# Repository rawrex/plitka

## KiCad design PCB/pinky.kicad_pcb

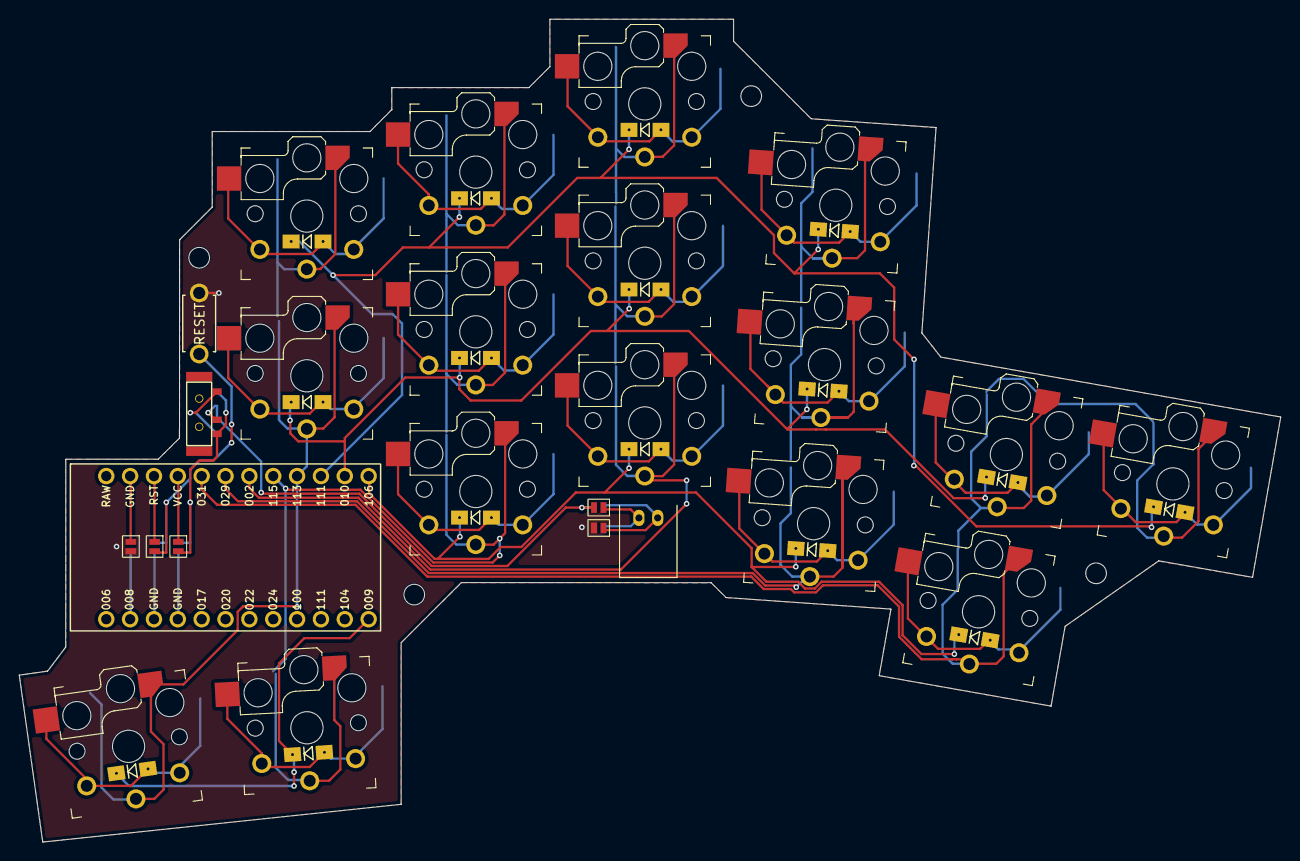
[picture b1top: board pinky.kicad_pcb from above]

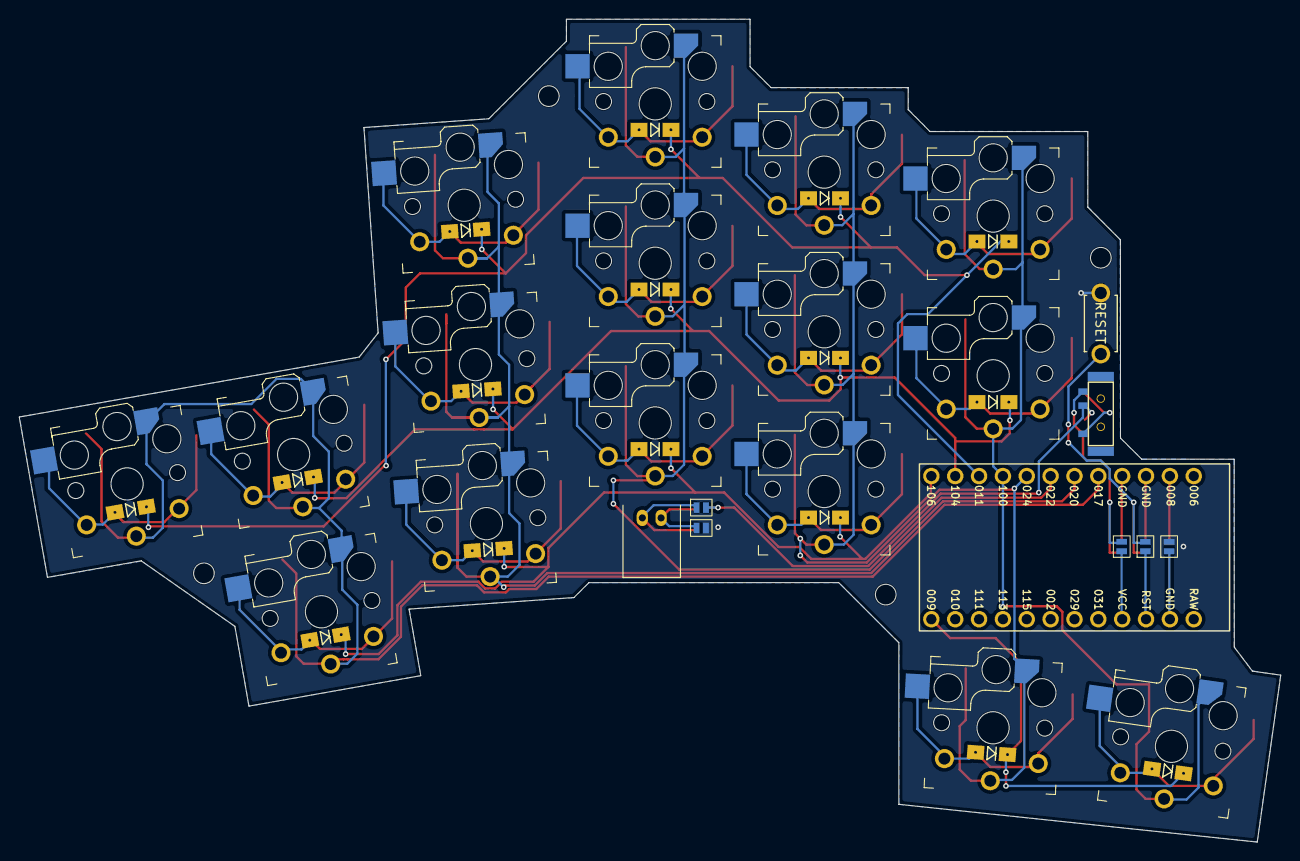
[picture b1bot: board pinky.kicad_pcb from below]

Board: 2 copper layers, 134.3 x 87.6 mm, 50 parts (6 on the bottom side), 34 nets.

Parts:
BT1: JST_PH
D1, D2, D4, D5, D6, D7, D8, D9, D10, D11, D12, D13, D14, D15, D16, D17: D; D_SOD123
H1, H2, H3, H4: MountingHole_2.2mm_M2; MountingHole
JP1, JP2, JP3, JP4, JP5, JP6, JP7, JP8, JP9, JP10: SDA; Jumper
RESET19: Val**; ResetSW
SW2, SW3, SW5, SW6, SW7, SW8, SW9, SW10, SW11, SW12, SW13, SW14, SW15, SW16, SW17, SW18: SW_Kailh_Choc_PG1350; Switch
SW_PWR1: MSK12C02
U1: nice!nano; nice_nano

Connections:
+BATT: JP9.2, JP10.2, SW_PWR1.3 (A)
+BATT_indirect: JP9.1, JP10.1, U1.4 (GND), U1.16 (EXT_VCC)
/PAD1: BT1.1 (+), JP1.1, JP2.1
/PAD2: BT1.2 (-), JP3.1, JP4.1
GND: JP1.2, JP4.2, JP5.2, JP6.2, RESET19.1
GND_indirect: JP5.1, JP6.1, U1.2 (D0/P0.08), U1.14 (GND)
unnamed: D1.2 (A), SW2.2
unnamed: D2.2 (A), SW3.2
unnamed: D4.2 (A), SW5.2
unnamed: D5.2 (A), SW6.2
unnamed: D6.2 (A), SW7.2
unnamed: D7.2 (A), SW8.2
unnamed: D8.2 (A), SW9.2
unnamed: D9.2 (A), SW10.2
unnamed: D10.2 (A), SW11.2
unnamed: D11.2 (A), SW12.2
unnamed: D12.2 (A), SW13.2
unnamed: D13.2 (A), SW14.2
unnamed: D14.2 (A), SW15.2
unnamed: D15.2 (A), SW16.2
unnamed: D16.2 (A), SW17.2
unnamed: D17.2 (A), SW18.2
unnamed: JP2.2, JP3.2, SW_PWR1.2 (B)
RESET: JP7.2, JP8.2, RESET19.2
RESET_indirect: JP7.1, JP8.1, U1.3 (GND), U1.15 (RESET)
col_A: SW2.1, SW3.1, SW5.1, U1.9 (D6/P1.00)
col_B: SW6.1, SW7.1, SW8.1, SW9.1, U1.8 (D5/P0.24)
col_C: SW10.1, SW11.1, SW12.1, U1.7 (D4/P0.22)
col_D: SW13.1, SW14.1, SW15.1, U1.6 (D3/P0.20)
col_E: SW16.1, SW17.1, SW18.1, U1.5 (D2/P0.17)
row_A: D1.1 (K), D5.1 (K), D9.1 (K), D12.1 (K), D15.1 (K), U1.10 (D7/P0.11)
row_B: D2.1 (K), D6.1 (K), D10.1 (K), D13.1 (K), D16.1 (K), U1.11 (D8/P1.04)
row_C: D7.1 (K), D11.1 (K), D14.1 (K), D17.1 (K), U1.12 (D9/P1.06)
row_D: D4.1 (K), D8.1 (K), U1.24 (D10/P0.09)

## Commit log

2026-06-12 Metadata corrections
2026-06-12 Encoder removal
2026-06-12 Led removal
2026-06-12 Tenting puck and the version removal
2026-06-13 Cooper fill update after the custom battery removal
2026-06-16 Corrections to the symbol pads oredering and other definitions
2026-06-16 Corrected the references to the footprints
2026-06-17 Updated from pcb
2026-06-17 Mounting holes are just holes, without pads
2026-06-17 Grid alignment warning fix
2026-06-17 Scheme clean up
2026-06-17 Minor scheme clean ups
2026-06-17 Explicit Not Connected names
2026-06-17 Footprint type attribute is changed to smd
2026-06-17 Updates after footprint corrections
2026-06-17 Thermal relief issue solved
2026-06-17 Custom pad shapes to avoid conflicts with the drill holes
2026-06-17 Using updated pads
2026-06-18 Footprints corrections, clean ups, and aligments. Fixed unaligned components using the schematics of the real items
2026-06-18 Pulled updates of the footprints
2026-06-18 Removed the rudimentary switchplate files
2026-06-18 Footprint corrections, removed the incorrect configuration of the SMD diode
2026-06-19 Cooper layers count fixed
2026-06-19 Rudimentary symbols clean up
2026-06-19 Agents file update
2026-06-19 Footprint corrections and clean up
2026-06-19 Sym table update
2026-06-20 Further rudiments clean up
2026-06-20 Model files update
2026-06-20 Stopped tracking generated file
2026-06-20 Agents update
2026-06-21 Symbols rename and proper footprints assignment
2026-06-22 Footprint rename
2026-06-22 Footprints assigned
2026-06-22 Symbols rename
2026-06-22 PCB pulled updates
2026-06-22 Corrected the items counts
2026-06-22 Minor text repositions
2026-06-26 Switch footprint with 3D model of the switch
2026-06-26 Removing islands option set
2026-06-26 Mounting holes positioning
2026-06-29 Pins reordering to aid routing
2026-06-29 Routing done
2026-06-29 Route to hole clearance error resolution
2026-06-29 One more edge clearance fix
2026-06-29 Pulled updates
2026-06-29 Work in progress on shaping up the edges
2026-06-29 Autoheal applied
2026-06-30 More shape edits
2026-06-30 Fixed the missing connections between diodes on both layers
2026-06-30 Net specifications for the double sided configuration. DRC errors resolved
2026-06-30 Added few explicit, stitching, vias to the GND fill
2026-06-30 Silkscreen layer references removed from the nicenano pads
2026-06-30 Footprint clean up
2026-06-30 Courtyard to the reset button
2026-06-30 MountingHole clean up and courtyard to B added
